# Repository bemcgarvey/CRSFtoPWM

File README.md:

# CRSFtoPWM  
  
A board to provide up to 10 PWM servo outputs using an inexpensive serial ELRS receiver.  Tested with a BetaFPV Nano 2400 Rx  
Includes a pressure sensor for baro altitude and vertical speed telemetery. 
  
### Features:  
* 8 PWM servo outputs with adjustable update rate from 50Hz to 333Hz
* 2 PWM outputs fixed at 50Hz
* All pwm outputs can be mapped to any channel
* Optional SBus output of all channels
* Altitude and VSpeed telemetry over ELRS/CRSF
* Rx battery telemetry over ELRS
* Vbat from 2S to 6S or optionally from servo rail
* Extra UART port can be configured for gps telemetry, debugging, or Betaflight passthrough for ELRS rx firmware updates
* Extra I2C port for future expansion?
* Windows client software for configuration over a USB-Serial (FTDI etc.) connection.

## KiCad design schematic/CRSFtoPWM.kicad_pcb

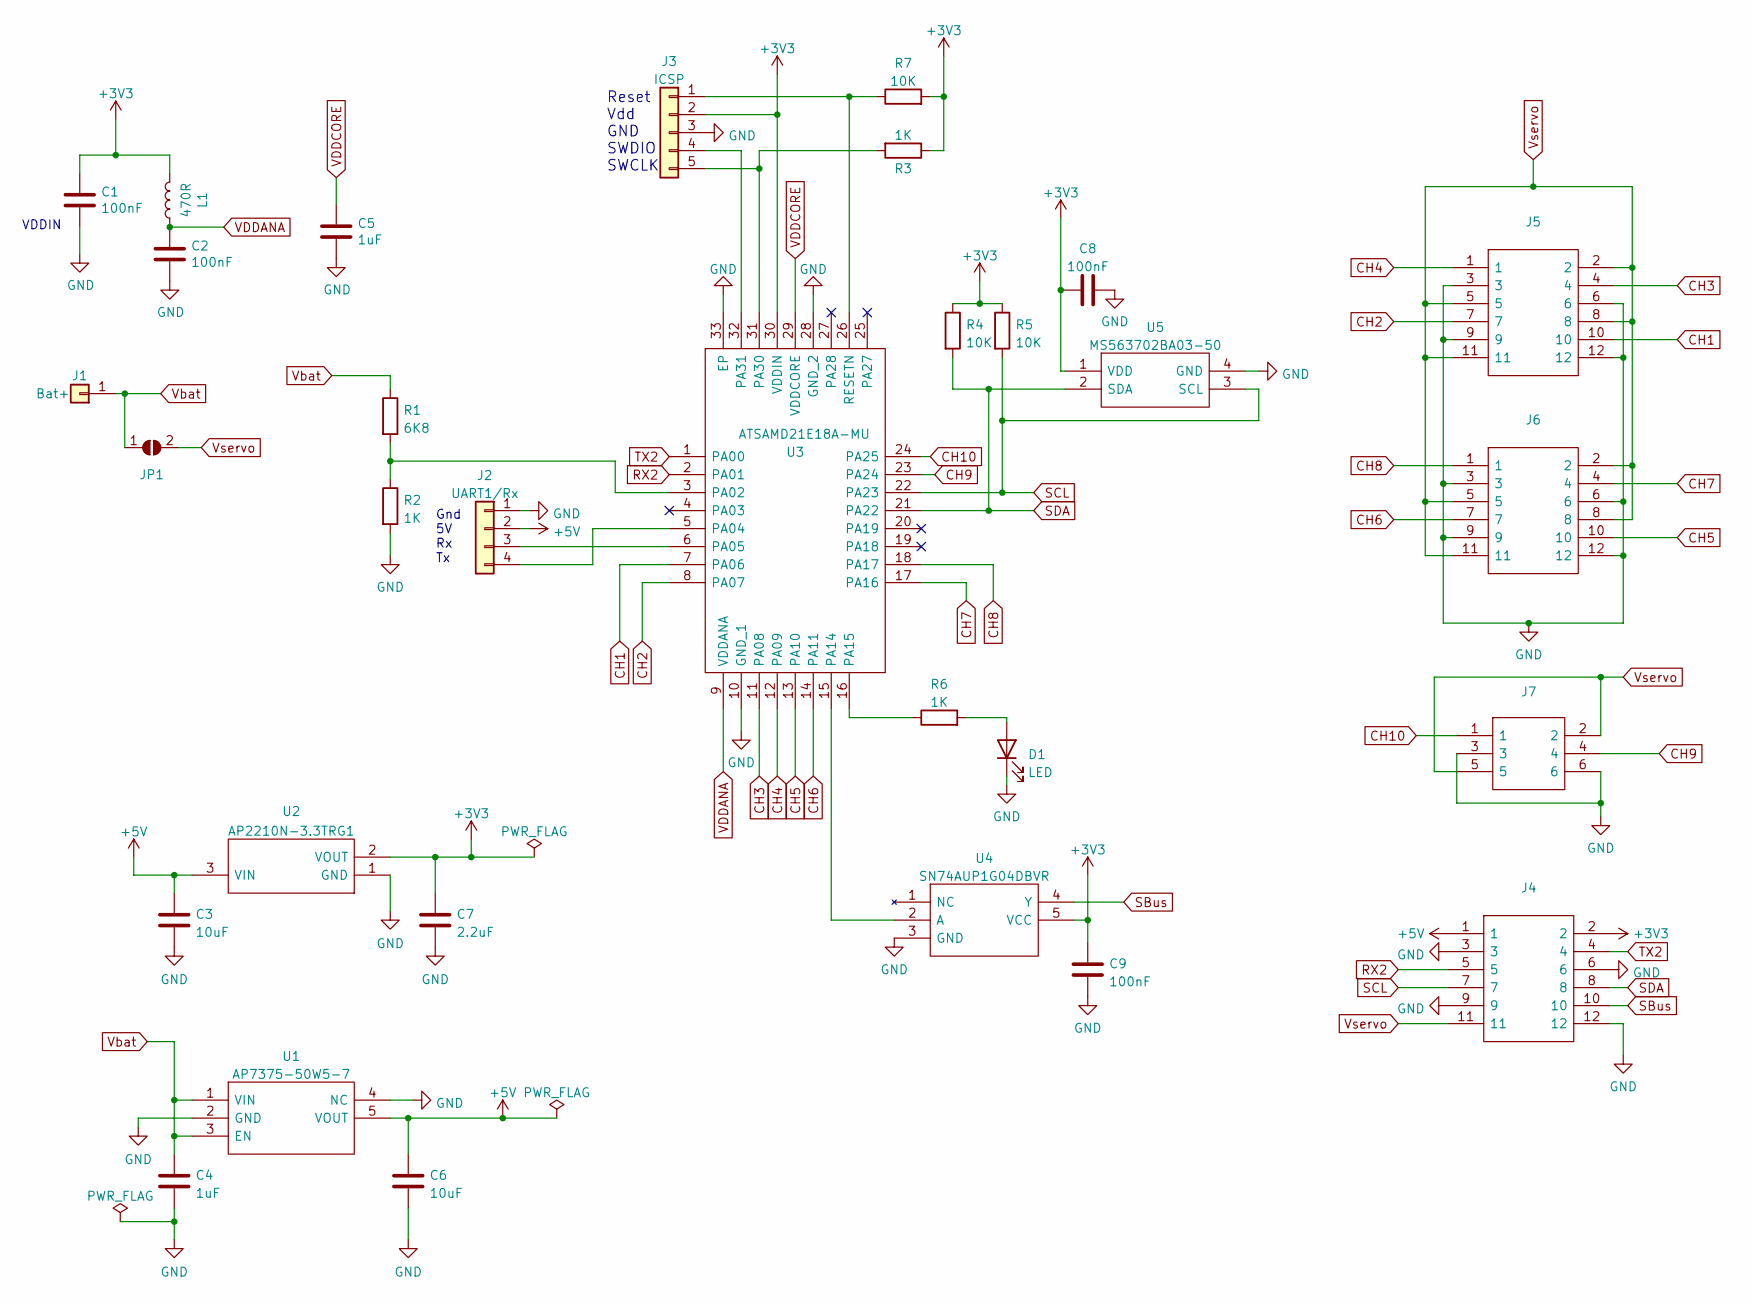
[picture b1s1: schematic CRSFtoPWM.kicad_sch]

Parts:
C1, C2, C8, C9: 100nF; C_0402_1005Metric
C3, C6: 10uF; C_0603_1608Metric
C4: 1uF; C_0603_1608Metric
C5: 1uF; C_0402_1005Metric
C7: 2.2uF; C_0603_1608Metric
D1: LED; LED_0603_1608Metric
J1: Bat+; PinHeader_1x01_P2.54mm_Vertical
J2: UART1/Rx; PinHeader_1x04_P2.54mm_Vertical
J3: ICSP; PinHeader_1x05_P2.54mm_Vertical
J4, J5, J6: TSW-104-08-G-T-RA; HDRRA12W64P254_3X4_1016X254X810P; Mouser Part Number 200-TSW10408GTRA
J7: TSW-102-08-L-T-RA; HDRRA6W64P254_3X2_508X254X810P; Mouser Part Number 200-TSW10208LTRA
JP1: SolderJumper_2_Open; SolderJumper-2_P1.3mm_Open_RoundedPad1.0x1.5mm
L1: 470R; L_0603_1608Metric
R1: 6K8; R_0603_1608Metric
R2, R3, R6: 1K; R_0603_1608Metric
R4, R5, R7: 10K; R_0603_1608Metric
U1: AP7375-50W5-7; SOT95P285X140-5N; Mouser Part Number 621-AP7375-50W5-7
U2: AP2210N-3.3TRG1; SOT95P280X145-3N; Mouser Part Number 621-AP2210N-3.3TRG1
U3: ATSAMD21E18A-MU; QFN50P500X500X100-33N-D; Mouser Part Number 556-ATSAMD21E18A-MU
U4: SN74AUP1G04DBVR; SOT95P280X145-5N; Mouser Part Number 595-SN74AUP1G04DBVR
U5: MS563702BA03-50; MS5637_1; Mouser Part Number 824-MS563702BA03-50

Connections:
+3V3: C1.1, C7.1, C8.1, C9.1, J3.2, J4.2, L1.2, R3.1, R4.1, R5.1, R7.2, U2.2 (VOUT), U3.30 (VDDIN), U4.5 (VCC), U5.1 (VDD)
+5V: C3.1, C6.1, J2.2, J4.1, U1.5 (VOUT), U2.3 (VIN)
CH1: J5.10, U3.7 (PA06)
CH2: J5.7, U3.8 (PA07)
CH3: J5.4, U3.11 (PA08)
CH4: J5.1, U3.12 (PA09)
CH5: J6.10, U3.13 (PA10)
CH6: J6.7, U3.14 (PA11)
CH7: J6.4, U3.17 (PA16)
CH8: J6.1, U3.18 (PA17)
CH9: J7.4, U3.23 (PA24)
CH10: J7.1, U3.24 (PA25)
GND: C1.2, C2.2, C3.2, C4.2, C5.2, C6.2, C7.2, C8.2, C9.2, D1.1 (K), J2.1, J3.3, J4.3, J4.6, J4.9, J4.12, J5.3, J5.6, J5.9, J5.12, J6.3, J6.6, J6.9, J6.12, J7.3, J7.6, R2.2, U1.2 (GND), U1.4 (NC), U2.1 (GND), U3.10 (GND_1), U3.28 (GND_2), U3.33 (EP), U4.3 (GND), U5.4 (GND)
unnamed: D1.2 (A), R6.2
unnamed: J2.3, U3.6 (PA05)
unnamed: J2.4, U3.5 (PA04)
unnamed: J3.1, R7.1, U3.26 (RESETN)
unnamed: J3.4, U3.32 (PA31)
unnamed: J3.5, R3.2, U3.31 (PA30)
unnamed: R1.2, R2.1, U3.3 (PA02)
unnamed: R6.1, U3.16 (PA15)
unnamed: U3.15 (PA14), U4.2 (A)
RX2: J4.5, U3.2 (PA01)
SBus: J4.10, U4.4 (Y)
SCL: J4.7, R5.2, U3.22 (PA23), U5.3 (SCL)
SDA: J4.8, R4.2, U3.21 (PA22), U5.2 (SDA)
TX2: J4.4, U3.1 (PA00)
VDDANA: C2.1, L1.1, U3.9 (VDDANA)
VDDCORE: C5.1, U3.29 (VDDCORE)
Vbat: C4.1, J1.1, JP1.1 (A), R1.1, U1.1 (VIN), U1.3 (EN)
Vservo: J4.11, J5.2, J5.5, J5.8, J5.11, J6.2, J6.5, J6.8, J6.11, J7.2, J7.5, JP1.2 (B)

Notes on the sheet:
Reset Vdd GND SWDIO SWCLK
Gnd 5V Rx Tx
VDDIN

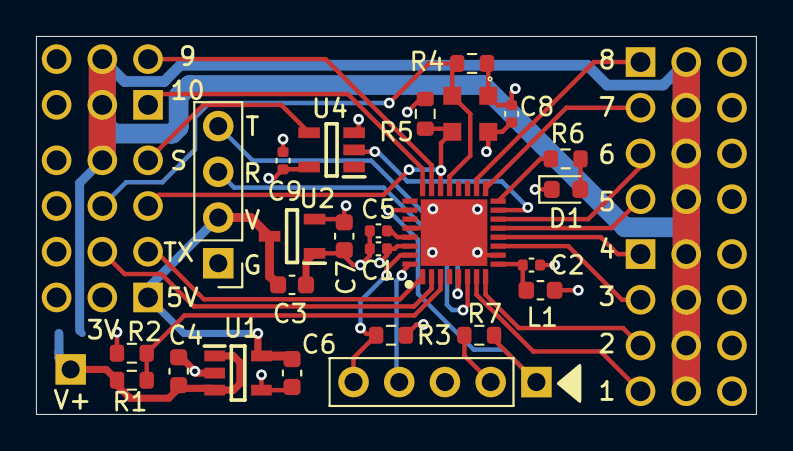
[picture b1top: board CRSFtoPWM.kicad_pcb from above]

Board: 4 copper layers, 40.0 x 21.0 mm, 31 parts (1 on the bottom side), 31 nets.

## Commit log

2023-01-26 Initial KiCad project
2023-01-26 Initial firmware
2023-01-26 Initial pins and modules
2023-01-30 Updated Harmony config
2023-01-31 Draft schematic
2023-01-31 Pin updates
2023-01-31 Changed ICSP pullups
    per datasheet
2023-01-31 Added two more outputs
2023-01-31 Added TC5 for two more outputs
2023-01-31 Footprints assigned
2023-01-31 Updated some footprints
2023-02-01 Changed connections to improve pcb layout
2023-02-01 Initial pcb parts layout
    Also fixed VDDANA
    Made some schematic changes to improve layout
2023-02-01 Pcb fully routed - needs optimization
2023-02-02 Smaller pcb and tweaks
2023-02-03 Added text, minor tweaks
2023-02-04 Improved Vservo current capacity
2023-02-04 Improved Rx,Tx traces
2023-02-04 Improved SCL,SDA traces
2023-02-04 Added pullup to RESET
    Updated pins in Harmony
2023-02-05 Fixed JLC text
2023-02-07 Fixed fill zones
2023-03-13 Generated gerbers
2023-04-01 Generated BOM
2023-04-02 Made labels consistent
2023-04-02 Updated BOM
2023-04-03 Initial test code
    Added FreeRTOS code
    Fixed ELRS baud
2023-04-04 Tested pressure sensor
2023-04-04 Removed firmware project
    Need to redo project with FreeRTOS from the start
2023-04-04 Revert "Removed firmware project"
    This reverts commit d749c80b13bd2d3b8b714d2042c8b0bbf96a704e.
2023-04-04 FreeRTOS working
2023-04-04 Setup task structure
2023-04-05 Settings and debug messages implemented
2023-04-05 vBat working
2023-04-05 Altitude working
2023-04-07 Initial rx code working
2023-04-07 Updated schematic to correct channel numbering
2023-04-07 Outputs 1-8 working
2023-04-08 All outputs and telemetry working
2023-04-08 DMA working
2023-04-08 Improved altitude calculations
2023-04-08 Improved DMA handling
2023-04-09 SaveSettings working
2023-04-09 Initial client project
2023-04-09 Serial port connecting
2023-04-10 Serial communication working
2023-04-10 Changed power circuit
    3.3V regulator now uses regulated 5V for input. Less load on 3.3V regulator and only the 5V regulator has high voltage input.
2023-04-10 Changed input cap back to 0603 and new gerbers
2023-04-10 Added jumper to allow power from VServo
2023-04-11 Improved debugMsg
    Now uses printf format
2023-04-11 Read and save settings working
2023-04-12 Voltage calibration working
2023-04-13 Added icon and About dialog
2023-04-13 WDT enabled
2023-04-13 Watchdog improved
2023-04-13 Added file headers
2023-04-14 Improved vario calculations
2023-04-14 Improved serial handling
2023-04-14 Removed unused member
2023-04-14 Fixed serial detect
2023-04-15 Improved output calculations
2023-04-15 Improved pressure calculations
2023-04-28 Simplified pressure calculations
2023-04-29 Initial CLI working
2023-04-30 Passthrough mostly working
2023-04-30 Removed reboot - software does it
2023-05-01 Exit passthrough gracefully
2023-05-01 Reset default settings to original values
2023-05-02 Added change log. Set firmware to V1.1
2023-05-02 Some clean up
2023-05-03 Improved passthrough
2023-05-05 Created ISR for both passthrough and gps
    Increased passthrough queue sizes
    Improved baud rate change function
2023-05-07 Added gps telemetry
2023-05-10 Changed comments to V 1.1
2023-05-11 Set default uart mode to passthrough
2023-06-01 Added gps baud options
2023-06-02 Improved NMEA parsing
2023-06-02 Fixed a typo
2023-07-27 Fixed uart error handler bug
